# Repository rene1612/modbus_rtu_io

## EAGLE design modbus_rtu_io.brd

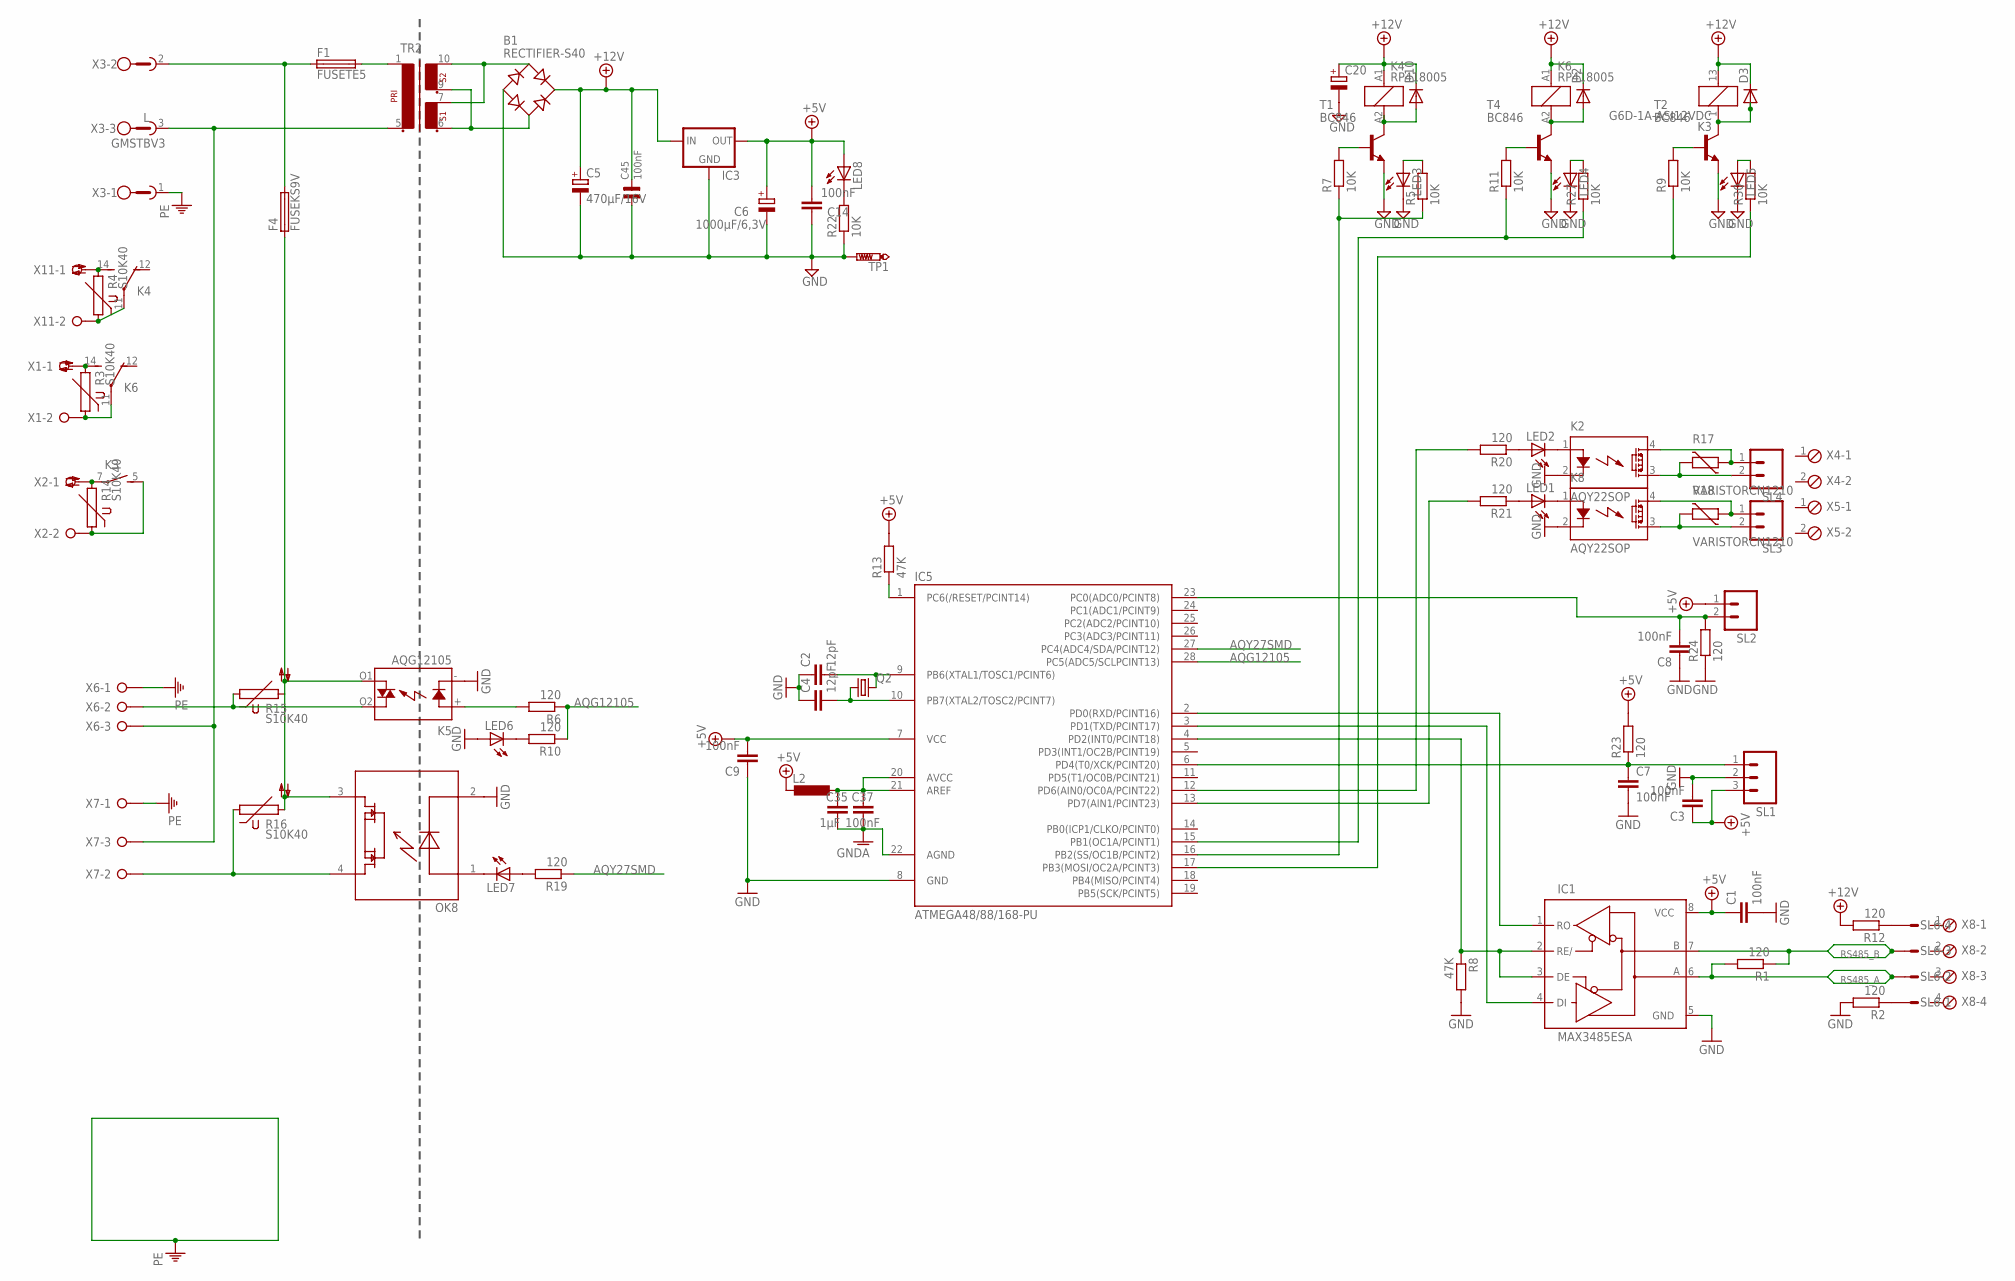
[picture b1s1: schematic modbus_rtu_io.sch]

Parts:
B1: RECTIFIER-S40; TO-269AA
C1, C3, C7, C8, C9, C37: 100nF; C0603
C2, C4: 12pF; C0805
C5: 470µF/16V; E3,5-8
C6: 1000µF/6,3V; E3,5-8
C14: 100nF; C1206
C20: CPOL-EUE3.5-8; E3,5-8
C35: 1µF; C0603
C45: 100nF; C0805
D2, D3, D10: DIODE-MINIMELF; MINIMELF
F1: FUSETE5; TE5
F4: FUSEKS9V; KS9V
IC1: MAX3485ESA; SO08
IC3: 78XXS
IC5: ATMEGA48/88/168-PU; DIL28-3
K2, K8: AQY22SOP; SOP04
K3: G6D-1A-ASI12VDC; G6D
K4, K6: RP418005; RT-C/O12A3.5
K5: AQG12105; AQG
L2: L-EUL0805; L0805
LED1, LED2, LED3, LED4, LED5, LED6, LED7, LED8: LED3MM
OK8: AQY280; DIL4-SMD
Q2: CRYTALHC49S; HC49/S
R1, R2, R6, R10, R12, R19, R20, R21, R23, R24: 120; R0603
R3, R4, R14, R15, R16: S10K40
R5, R7, R9, R11, R22, R27, R30: 10K; R0603
R8, R13: 47K; R0603
R17, R18: VARISTORCN1210; CT/CN1210
SL1: M03; 03P
SL2, SL3, SL4: M02; 02P
SL6: M04S; 04P
T1, T2, T4: BC846; SOT23
TP1: PTR1PAD1-13; P1-13
TR2: EI30-2
X1, X2, X11: W237-02P; W237-132
X3: GMSTBV3
X4, X5: MPT2; 2POL254
X6, X7: W237-03P; W237-133
X8: MPT4; 4POL254

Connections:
+5V: C1.1, C3.1, C6.+, C9.2, C14.2, IC1.8 (VCC), IC3.OUT, IC5.7 (VCC), L2.2, LED8.A, R13.2, R23.2, SL1.3, SL2.1
+12V: B1.+, C5.+, C20.+, C45.2, D2.C, D3.C, D10.C, IC3.IN, K3.13 (2), K4.A1 (1), K6.A1 (1), R12.2
AQG12105: IC5.28 (PC5(ADC5/SCLPCINT13)), R6.1, R10.1
AQY27SMD: IC5.27 (PC4(ADC4/SDA/PCINT12)), R19.1
AVCC: C35.1, C37.1, IC5.20 (AVCC), IC5.21 (AREF), L2.1
GND: B1.-, C1.2, C2.1, C3.2, C4.1, C5.-, C6.-, C7.2, C8.1, C9.1, C14.1, C20.-, C45.1, IC1.5 (GND), IC3.GND, IC5.8 (GND), K2.2 (K), K5.- (K), K8.2 (K), LED3.K (C), LED4.K (C), LED5.K (C), LED6.A, OK8.2, R2.2, R8.2, R22.1, R24.1, SL1.2, T1.2 (E), T2.2 (E), T4.2 (E), TP1.TP
GNDA: C35.2, C37.2, IC5.22 (AGND)
L: F1.1, F4.2, X3.2
unnamed: C2.2, IC5.9 (PB6(XTAL1/TOSC1/PCINT6)), Q2.2
unnamed: R9.2, T2.1 (B)
unnamed: LED3.A, R5.2
unnamed: K4.11, R4.1, X11.2
unnamed: K4.14 (S), R4.2, X11.1
unnamed: K6.14 (S), R3.2, X1.1
unnamed: R7.2, T1.1 (B)
unnamed: R2.1, SL6.1
unnamed: IC1.1 (RO), IC5.2 (PD0(RXD/PCINT16))
unnamed: IC1.4 (DI), IC5.3 (PD1(TXD/PCINT17))
unnamed: D10.A, K4.A2 (2), T1.3 (C)
unnamed: D3.A, K3.1, T2.3 (C)
unnamed: R11.2, T4.1 (B)
unnamed: D2.A, K6.A2 (2), T4.3 (C)
unnamed: IC1.2 (RE/), IC1.3 (DE), IC5.4 (PD2(INT0/PCINT18)), R8.1
unnamed: K8.4 (DS1), R18.1, SL3.1
unnamed: C4.2, IC5.10 (PB7(XTAL2/TOSC2/PCINT7)), Q2.1
unnamed: K8.3 (DS2), R18.2, SL3.2
unnamed: B1.AC1, TR2.7 (4), TR2.10 (6)
unnamed: K2.4 (DS1), R17.1, SL4.1
unnamed: K2.3 (DS2), R17.2, SL4.2
unnamed: B1.AC2, TR2.6 (3), TR2.9 (5)
unnamed: F1.2, TR2.1
unnamed: K6.11, R3.1, X1.2
unnamed: K3.7, R14.2, X2.1
unnamed: K3.5 (S), R14.1, X2.2
unnamed: K5.O2 (DS1), R15.1, X6.2
unnamed: TR2.5 (2), X3.3, X6.3, X7.3
unnamed: OK8.4, R16.1, X7.2
unnamed: K5.+ (A), R6.2
unnamed: LED7.K (C), OK8.1
unnamed: K2.1 (A), LED2.K (C)
unnamed: F4.1, K5.O1 (DS2), OK8.3, R15.2, R16.2
unnamed: LED4.A, R27.2
unnamed: K8.1 (A), LED1.K (C)
unnamed: IC5.16 (PB2(SS/OC1B/PCINT2)), R5.1, R7.1
unnamed: IC5.12 (PD6(AIN0/OC0A/PCINT22)), R20.2
unnamed: IC5.13 (PD7(AIN1/PCINT23)), R21.2
unnamed: IC5.15 (PB1(OC1A/PCINT1)), R11.1, R27.1
unnamed: IC5.17 (PB3(MOSI/OC2A/PCINT3)), R9.1, R30.1
unnamed: LED1.A, R21.1
unnamed: LED2.A, R20.1
unnamed: LED7.A, R19.2
unnamed: LED6.K (C), R10.2
unnamed: R12.1, SL6.4
unnamed: LED5.A, R30.2
unnamed: LED8.K (C), R22.2
unnamed: C7.1, IC5.6 (PD4(T0/XCK/PCINT20)), R23.1, SL1.1
unnamed: IC5.1 (PC6(/RESET/PCINT14)), R13.1
unnamed: C8.2, IC5.23 (PC0(ADC0/PCINT8)), R24.2, SL2.2
PE: X3.1, X6.1, X7.1
RS485_A: IC1.6 (A), R1.2, SL6.2
RS485_B: IC1.7 (B), R1.1, SL6.3

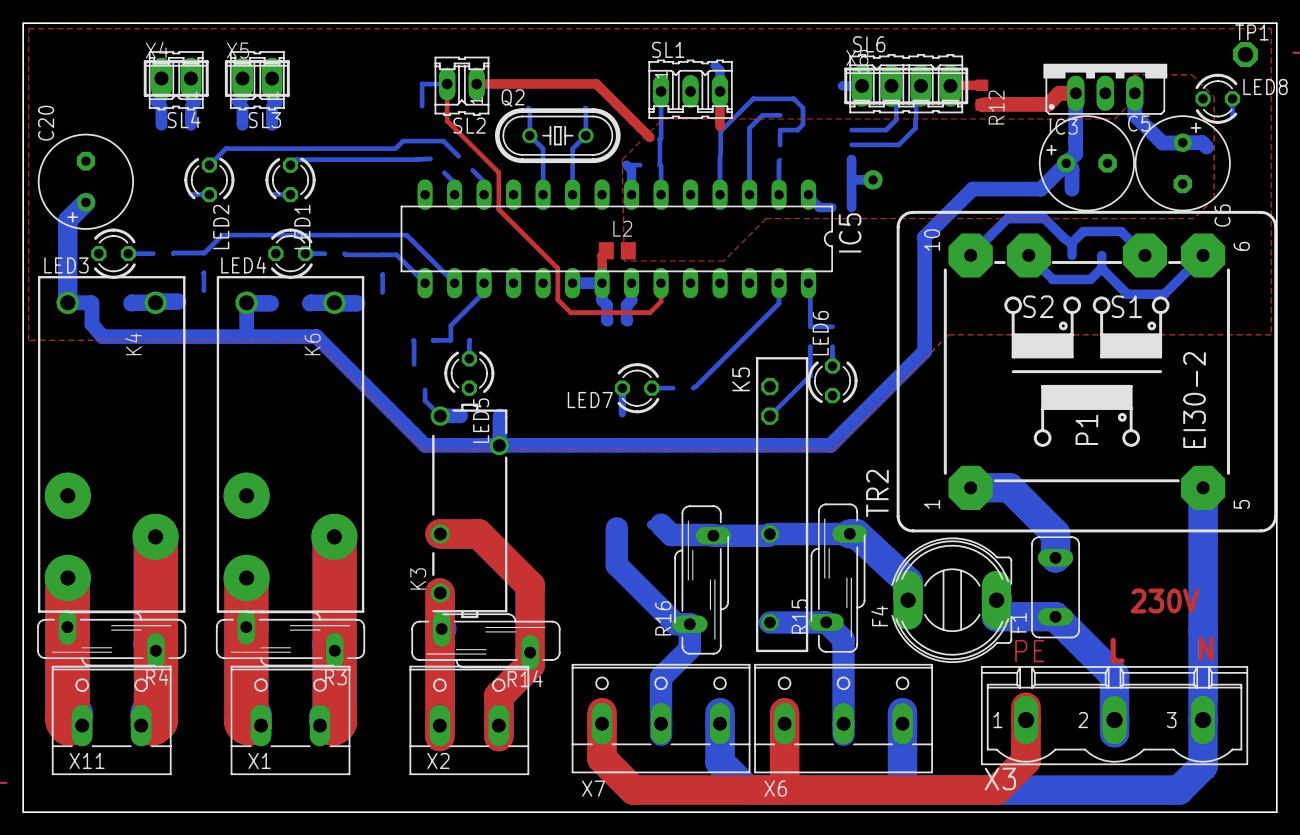
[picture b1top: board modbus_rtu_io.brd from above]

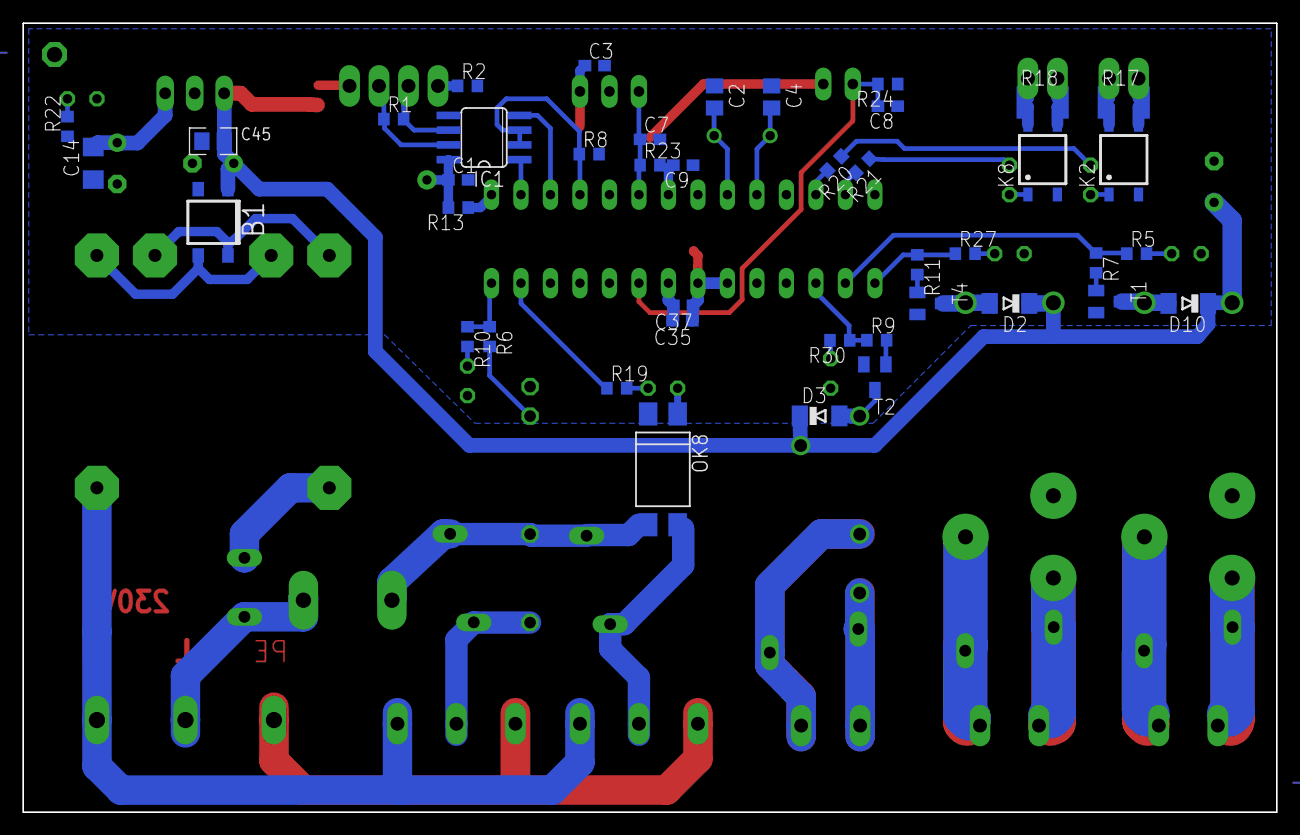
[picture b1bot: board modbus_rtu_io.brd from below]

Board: 2 copper layers, 108.0 x 67.9 mm, 87 parts (42 on the bottom side), 61 nets.

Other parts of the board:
U$1, U$2: PASS-ROUND

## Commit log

2018-05-03 erstes commit, schaltung fast fertig, pcb arangiert
2018-05-04 Relais geändert, Routing angefangen
2018-05-06 routing fertig
2018-05-07 opto-mosfet package berichtigt, fertigung vorbereitet
